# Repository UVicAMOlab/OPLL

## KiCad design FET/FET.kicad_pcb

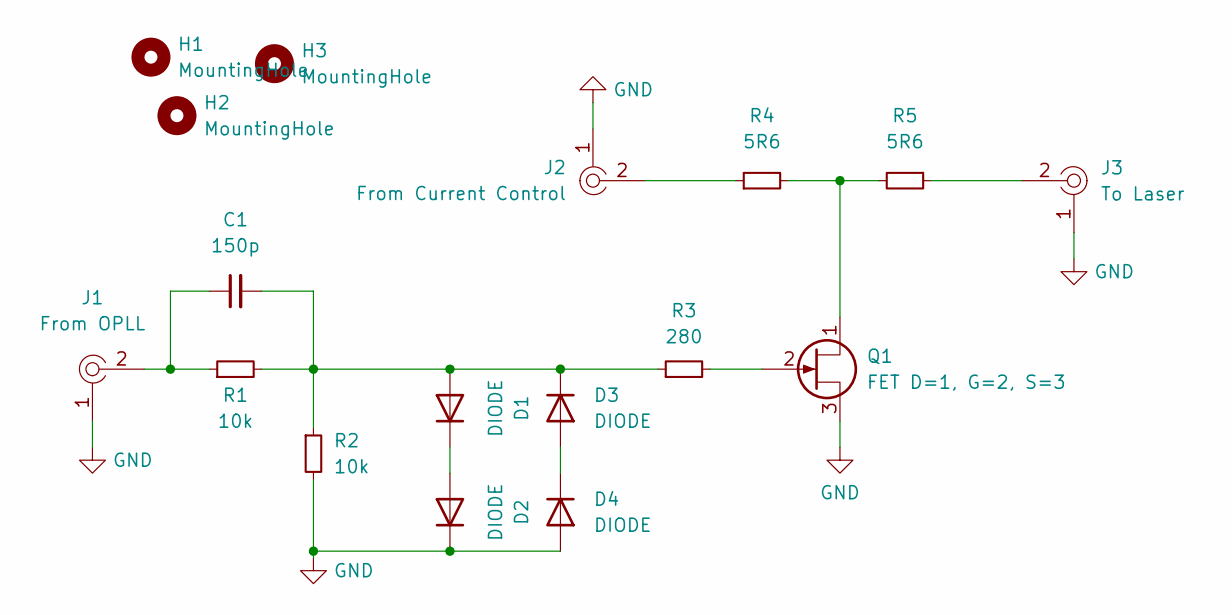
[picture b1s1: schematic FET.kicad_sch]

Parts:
C1: 150p; C_1206_3216Metric_Pad1.33x1.80mm_HandSolder
D1, D2, D3, D4: DIODE; D_1206_3216Metric_Pad1.42x1.75mm_HandSolder
H1, H2, H3: MountingHole; MountingHole_3.2mm_M3_Pad
J1: From OPLL; RF_SMA_Vertical_5-1814832-1; MPN 5-1814400-1; Digi-Key_PN A97593-ND
J2: From Current Control; RF_SMA_Vertical_5-1814832-1; MPN 5-1814400-1; Digi-Key_PN A97593-ND
J3: To Laser; RF_SMA_Vertical_5-1814832-1; MPN 5-1814400-1; Digi-Key_PN A97593-ND
Q1: FET D=1, G=2, S=3; TO-92-3
R1, R2: 10k; R_1206_3216Metric_Pad1.30x1.75mm_HandSolder
R3: 280; R_1206_3216Metric_Pad1.30x1.75mm_HandSolder
R4, R5: 5R6; R_1206_3216Metric_Pad1.30x1.75mm_HandSolder

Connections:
GND: D2.2 (K), D4.1 (A), J1.1, J2.1, J3.1, Q1.3 (S), R2.2
unnamed: C1.1, J1.2, R1.1
unnamed: C1.2, D1.1 (A), D3.2 (K), R1.2, R2.1, R3.1
unnamed: D1.2 (K), D2.1 (A)
unnamed: D3.1 (A), D4.2 (K)
unnamed: J2.2, R4.1
unnamed: J3.2, R5.1
unnamed: Q1.1 (D), R4.2, R5.2
unnamed: Q1.2 (G), R3.2

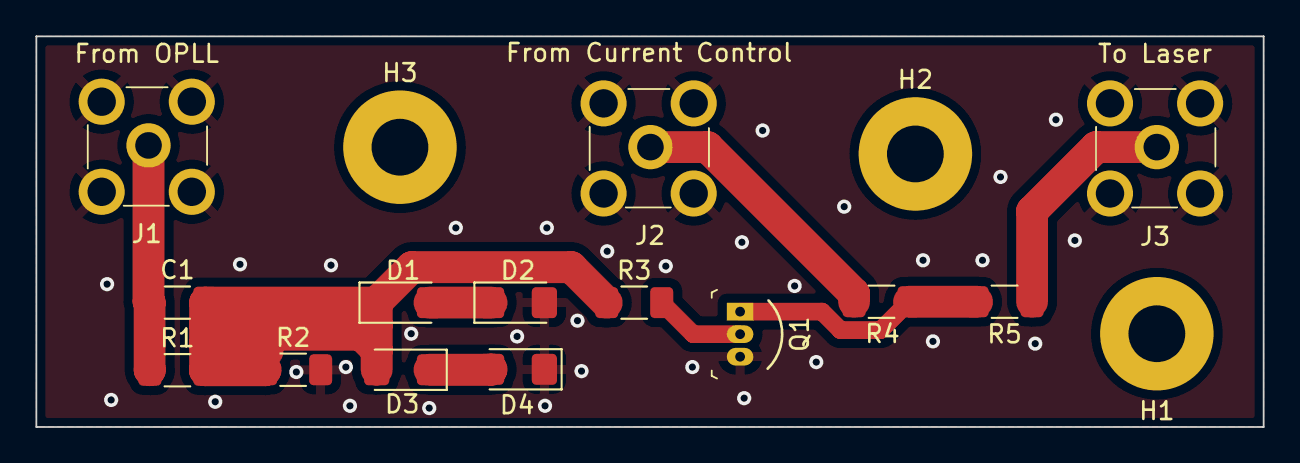
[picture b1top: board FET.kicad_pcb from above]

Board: 2 copper layers, 69.2 x 22.0 mm, 17 parts (0 on the bottom side), 9 nets.

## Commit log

2022-06-01 First OPLL iteration
2022-06-14 init
2022-06-15 FET update
